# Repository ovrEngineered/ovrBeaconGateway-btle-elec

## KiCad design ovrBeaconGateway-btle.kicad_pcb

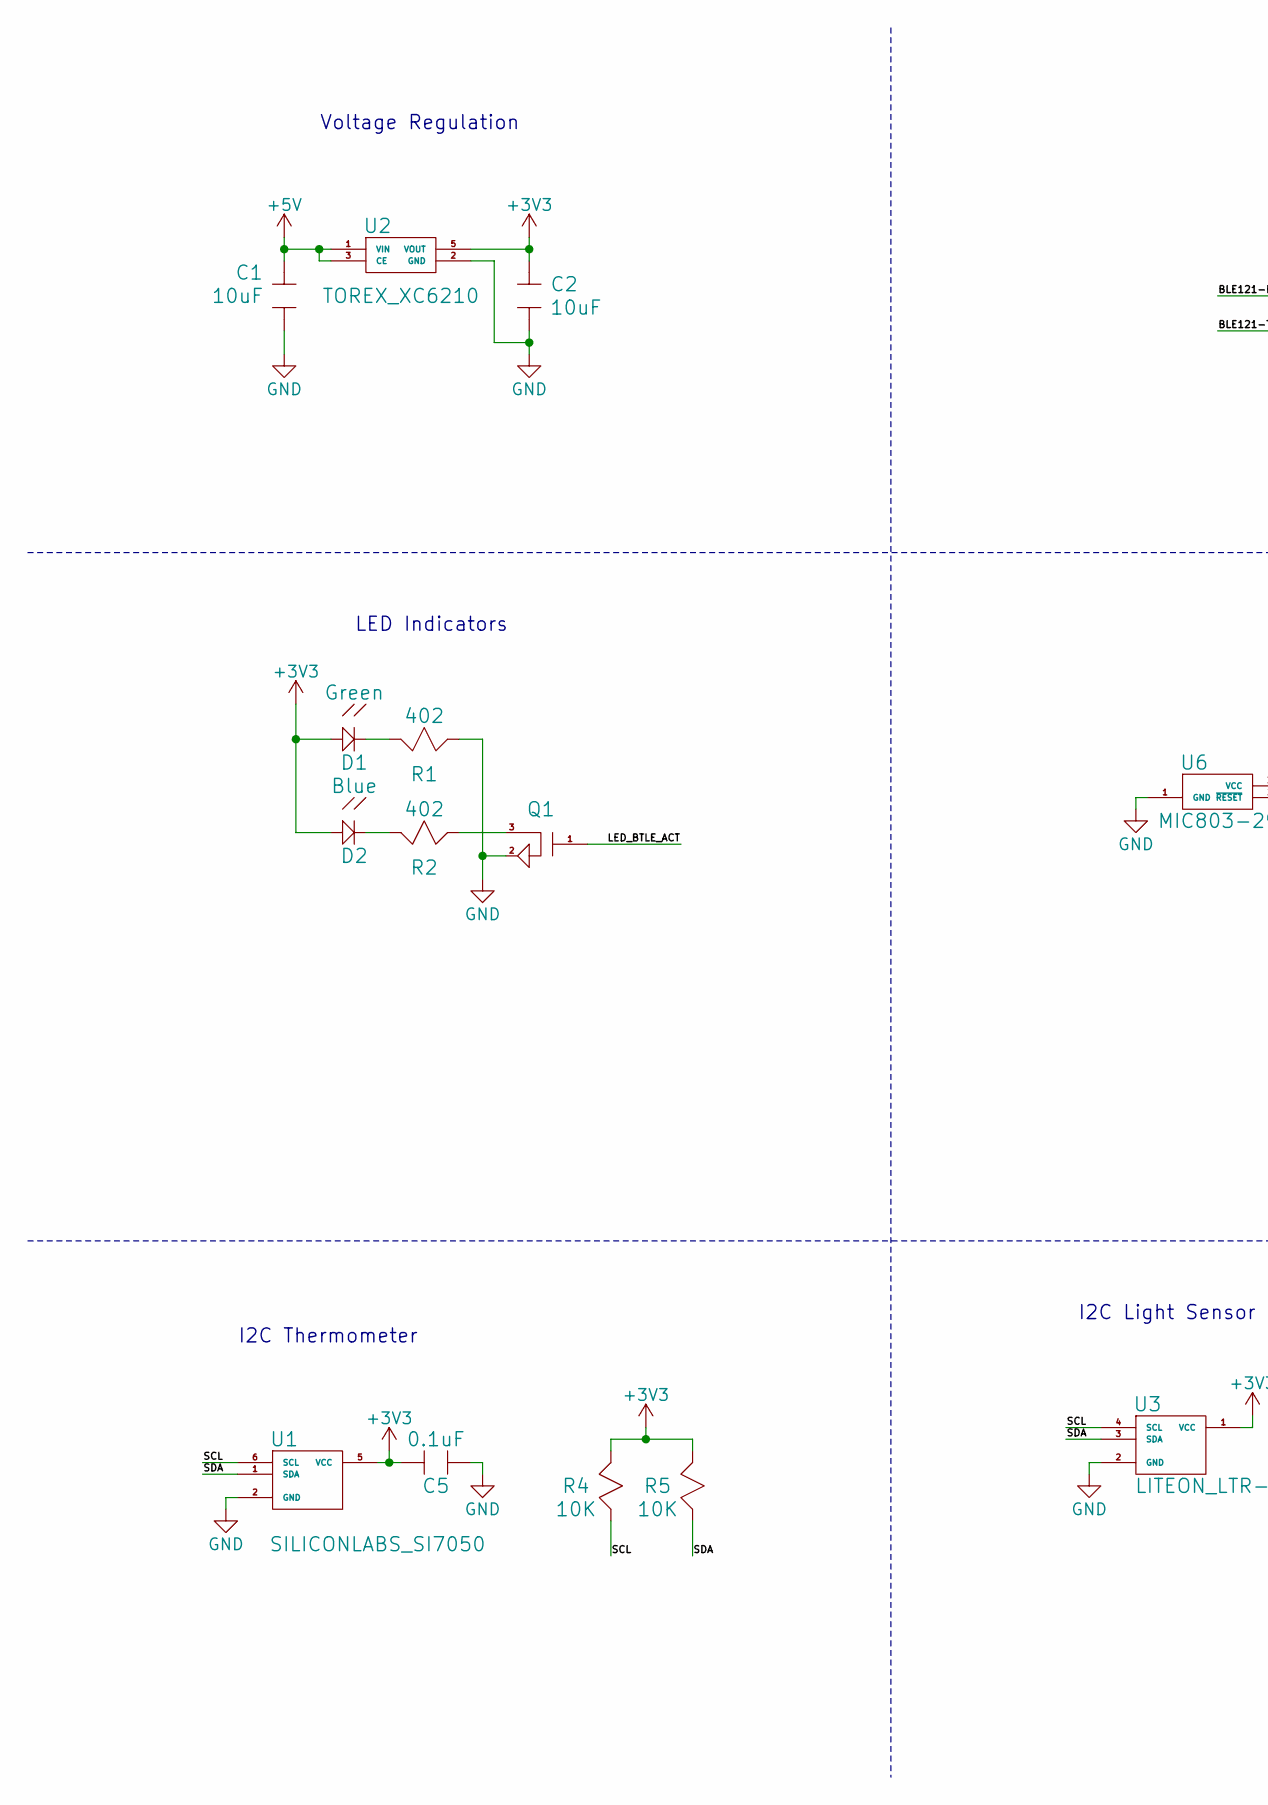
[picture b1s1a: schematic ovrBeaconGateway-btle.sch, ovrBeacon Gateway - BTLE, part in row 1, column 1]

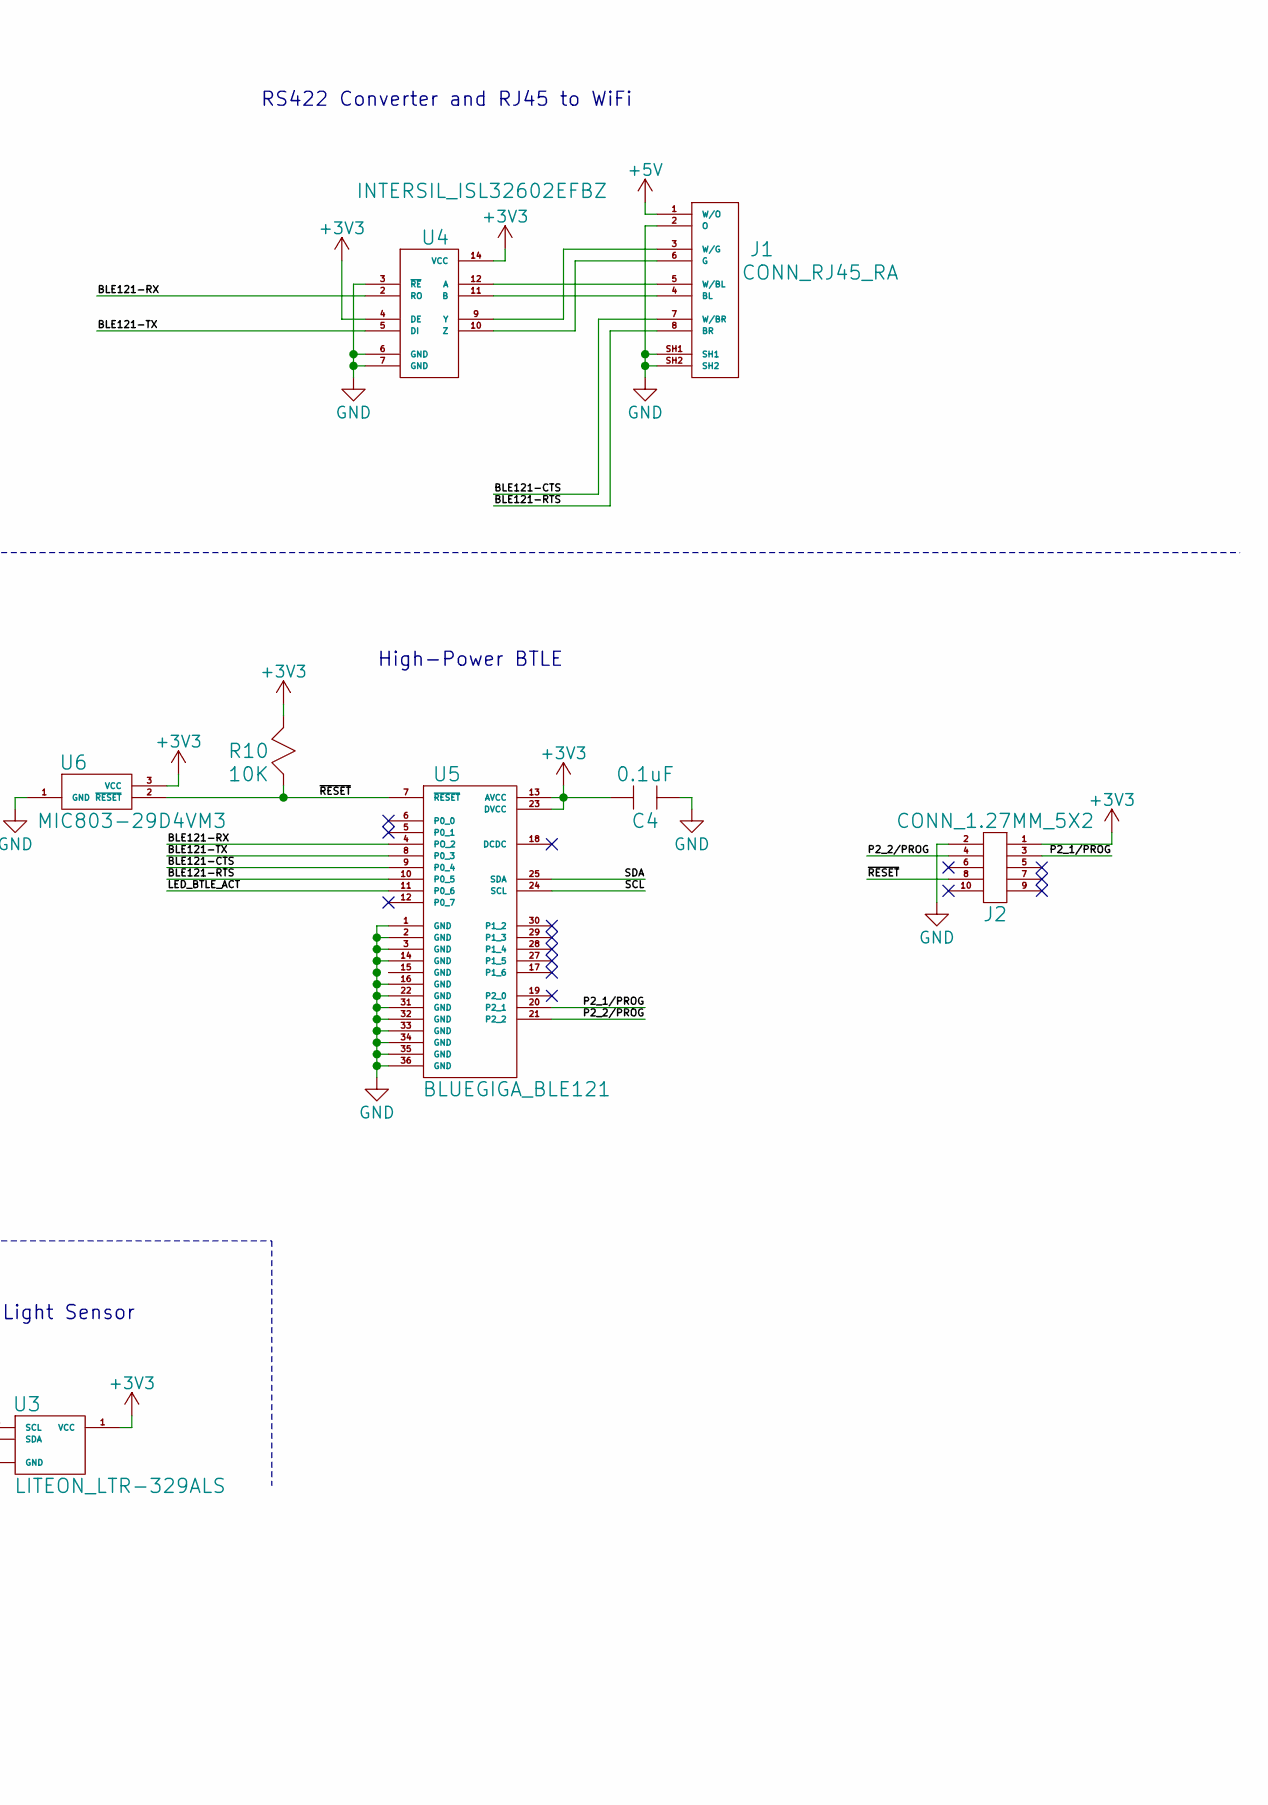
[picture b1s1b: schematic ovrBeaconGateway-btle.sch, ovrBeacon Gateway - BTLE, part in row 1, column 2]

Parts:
C1, C2: C_10uF_10v_0805; C_0805; Man. Part Num. GRM21BR71A106KE51L
C4, C5: C_0.1uF_10v_0603; C_0603; Man. Part Num. GRM188R71C104KA01D
D1: LED_GREEN_0603; D_0603; Man. Part Num. LTST-C193KGKT-5A
D2: LED_BLUE_0603; D_0603; Man. Part Num. LTST-C193TBKT-5A
J1: CONN_RJ45_RA; RJ45_NOMAG_RA; Man. Part Num. E6588-52L184-L
J2: CONN_1.27MM_5X2; 20021111-00010T4LF; Man. Part Num. 20021111-00010T4LF
Q1: FET_N_1.2A_20V; Man. Part Num. IRLML2402TRPBF
R1, R2: R_402_1%_0603; R_0603; Man. Part Num. CRCW0603402RFKEA
R4, R5, R10: R_10K_1%_0603; R_0603; Man. Part Num. CRCW060310K0FKEA
U1: SILICONLABS_SI7050; Man. Part Num. SI7050-A20-IM
U2: TOREX_XC6210; SOT-25-5; Man. Part Num. XC6210B332MR-G
U3: LITEON_LTR-329ALS; Man. Part Num. LTR-329ALS-01
U4: INTERSIL_ISL32602EFBZ; SOIC-14; Man. Part Num. ISL32602EFBZ
U5: BLUEGIGA_BLE121; BLE121; Man. Part Num. BLE121LR-A-M256K
U6: MIC803-29D4VM3; SOT-23-3; Man. Part Num. MIC803-29D4VM3-TR

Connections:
+3V3: C2.1, C4.1, C5.1, D1.1, D2.1, J2.1, R4.1, R5.1, R10.1, U1.5 (VCC), U2.5 (VOUT), U3.1 (VCC), U4.4 (DE), U4.14 (VCC), U5.13 (AVCC), U5.23 (DVCC), U6.3 (VCC)
+5V: C1.1, J1.1 (W/O), U2.1 (VIN), U2.3 (CE)
/BLE121-CTS: J1.7 (W/BR), U5.9 (P0_4)
/BLE121-RTS: J1.8 (BR), U5.10 (P0_5)
/BLE121-RX: U4.2 (RO), U5.4 (PO_2)
/BLE121-TX: U4.5 (DI), U5.8 (P0_3)
/LED_BTLE_ACT: Q1.1, U5.11 (P0_6)
/P2_1/PROG: J2.3, U5.20 (P2_1)
/P2_2/PROG: J2.4, U5.21 (P2_2)
/SCL: R4.2, U1.6 (SCL), U3.4 (SCL), U5.24 (SCL)
/SDA: R5.2, U1.1 (SDA), U3.3 (SDA), U5.25 (SDA)
/~RESET: J2.8, R10.2, U5.7 (~RESET), U6.2 (~RESET)
GND: C1.2, C2.2, C4.2, C5.2, J1.2 (O), J1.SH1, J1.SH2, J2.2, Q1.2, R1.1, U1.2 (GND), U2.2 (GND), U3.2 (GND), U4.3 (~RE), U4.6 (GND), U4.7 (GND), U5.1 (GND), U5.2 (GND), U5.3 (GND), U5.14 (GND), U5.16 (GND), U5.22 (GND), U5.31 (GND), U5.32 (GND), U5.33 (GND), U5.34 (GND), U5.35 (GND), U5.36 (GND), U6.1 (GND)
unnamed: D1.2, R1.2
unnamed: D2.2, R2.2
unnamed: J1.3 (W/G), U4.9 (Y)
unnamed: J1.4 (BL), U4.11 (B)
unnamed: J1.5 (W/BL), U4.12 (A)
unnamed: J1.6 (G), U4.10 (Z)
unnamed: Q1.3, R2.1

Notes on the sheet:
Voltage Regulation
LED Indicators
RS422 Converter and RJ45 to WiFi
High-Power BTLE
I2C Light Sensor
I2C Thermometer

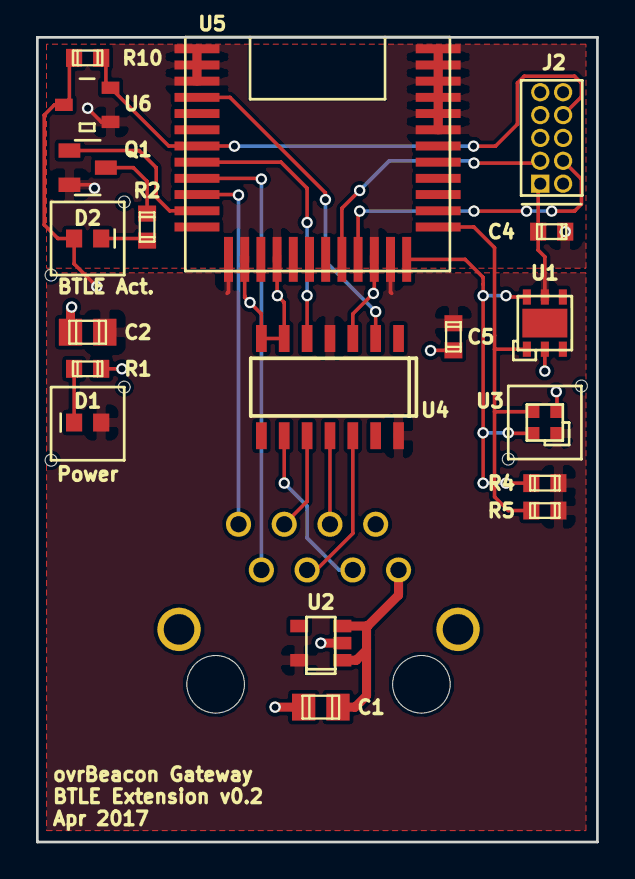
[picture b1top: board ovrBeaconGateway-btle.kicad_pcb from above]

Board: 2 copper layers, 31.1 x 44.7 mm, 20 parts (1 on the bottom side), 20 nets.

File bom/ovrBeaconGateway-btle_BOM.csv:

Reference,Value,Footprint,Datasheet,Manufacturer,Man. Part Num.,Supplier,Supplier Part Num.,Comp. Value,Quantity,
U4,INTERSIL_ISL32602EFBZ,ovrEngineered:SOIC-14,http://www.intersil.com/content/dam/Intersil/documents/fn79/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,Intersil,ISL32602EFBZ,Digi-Key,ISL32602EFBZ-ND,,1,
U5,BLUEGIGA_BLE121,ovrEngineered:BLE121,http://media.digikey.com/pdf/Data%20Sheets/BlueGiga%20PDFs/B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,BlueGiga,BLE121LR-A-M256K,Digi-Key,1446-1039-1-ND,,1,
J1,CONN_RJ45_RA,ovrEngineered:RJ45_NOMAG_RA,http://productfinder.pulseeng.com/products/datasheets/E6588-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,Pulse Electronics,E6588-52L184-L,Digi-Key,553-2265-ND,,1,
U2,TOREX_XC6210,ovrEngineered:SOT-25-5,https://www.torexsemi.com/file/xc6210/XC6210.pdf,Torex Semiconductor,XC6210B332MR-G,Digi-Key,893-1075-1-ND,,1,
C1 C2,C_10uF_10v_0805,ovrEngineered:C_0805,http://psearch.murata.com/capacitor/product/GRM21BR71A106KE5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,Murata,GRM21BR71A106KE51L,Digi-Key,490-3905-1-ND,10uF,2,
D1,LED_GREEN_0603,ovrEngineered:D_0603,http://optoelectronics.liteon.com/upload/download/DS22-2007-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,Lite-On Inc,LTST-C193KGKT-5A,Digi-Key,160-1828-1-ND,Green,1,
R1 R2,R_402_1%_0603,ovrEngineered:R_0603,http://www.vishay.com/docs/20035/dcrcwe3.pdf,Vishay_Dale,CRCW0603402RFKEA,Digi-Key,541-402HCT-ND,402,2,
C4 C5,C_0.1uF_10v_0603,ovrEngineered:C_0603,http://search.murata.co.jp/Ceramy/image/img/A01X/G101/ENG/GR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,Murata,GRM188R71C104KA01D,Digi-Key,490-1532-1-ND,0.1uF,2,
R10 R4 R5,R_10K_1%_0603,ovrEngineered:R_0603,http://www.vishay.com/docs/20035/dcrcwe3.pdf,Vishay_Dale,CRCW060310K0FKEA,Digi-Key,541-10.0KHCT-ND,10K,3,
U1,SILICONLABS_SI7050,ovrEngineered:SILICONLABS_SI7050,http://www.silabs.com/Support%20Documents/TechnicalDocs/Si70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,Silicon Labs,SI7050-A20-IM,Digi-Key,336-3118-5-ND,,1,
D2,LED_BLUE_0603,ovrEngineered:D_0603,http://optoelectronics.liteon.com/upload/download/DS22-2007-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,Lite-On Inc,LTST-C193TBKT-5A,Digi-Key,160-1827-1-ND,Blue,1,
Q1,FET_N_1.2A_20V,ovrEngineered:FET_N_1.2A_20V,http://www.irf.com/product-info/datasheets/data/irlml2402pbf.pdf,International Rectifier,IRLML2402TRPBF,Digi-Key,IRLML2402PBFCT-ND,,1,
U3,LITEON_LTR-329ALS,ovrEngineered:LITEON_LTR-329ALS,http://optoelectronics.liteon.com/upload/download/DS86-2014-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,Lite-On,LTR-329ALS-01,Digi-Key,160-2160-1-ND,,1,
J2,CONN_1.27MM_5X2,ovrEngineered:20021111-00010T4LF,http://portal.fciconnect.com/Comergent//fci/drawing/20021111.pdf,Amphenol,20021111-00010T4LF,Digi-Key,609-3712-ND,,1,
U6,MIC803-29D4VM3,ovrEngineered:SOT-23-3,http://www.microchip.com/mymicrochip/filehandler.aspx?ddocna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,Microchip Technology,MIC803-29D4VM3-TR,Digi-Key,576-3806-1-ND,,1,

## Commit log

2017-02-26 Initial commit…ready for DFM
2017-02-26 Added pricing and BOM
2017-02-26 Added schematic and layout PDF
2017-03-07 Updated pricing document w/ variants
2017-05-01 Out for DFM
